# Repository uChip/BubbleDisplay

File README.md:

# hp Bubble Display Controller  

___  

This is a board and firmware project supporting hp's 4 digit 7 segment LED bubble display, QDSP-6064, available from [SparkFun](https://www.sparkfun.com/products/12710).  The project is intended to enable a pair of displays to be easily connected over a two-wire I2C bus to a microcontroller (e.g. Arduino).  The board is also an example circuit of how to get reasonable brightness from these small displays.  By having a separate microcontroller driving the display, the burden (I/O pins, code space & CPU cycles) on the main application microcontroller is reduced.

For a more detailed write-up of the project see "Forum Postings.pdf" in the repo or see [this thread on the SparkFun forum](https://forum.sparkfun.com/viewtopic.php?f=14&t=38056).

Here is a photo of the functional display.  

This repo includes Eagle CAD PCB design files for the board, and Arduino source code for controller firmware and interface library with examples.  The board acts as an I2C slave driven from another microcontroller as I2C master.

## Order PCBs  

You can order this PCB directly from OSH Park.  Click on the following link.  
  * Bubble Display Controller - http://oshpark.com/shared_projects/Lmfa2Fmm 

See Bill of Materials file in repo for parts list.  

## Status  
  * 07APR2014 PCB received built and tested good.
  * Firmware, library and examples have been completed and tested against the final PCB.

## File Formats  

Design files are in "CadSoft EAGLE PCB Design Software" .brd and .sch formats.  
A free version of the software can be downloaded from www.cadsoftusa.com.  

schematic  

PCB   

Firmware, library and examples were developed using the [Arduino](http://arduino.cc/) 1.0.5-r2 IDE and the source files are in Arduino .ino format (and .h or .cpp formats as applicable).

## Distribution License  

You may use this PCB design and source code however you like but no liability is accepted.  

## Attributions

The hardware design has roots in the SparkFun [RedBoard](https://www.sparkfun.com/products/11575) design.  

The firmware is based on the slave_receiver.ino example and relies upon the wire library from Arduino, both included as part of the Arduino distribution.  The SparkFun tutorial [Using the Serial 7-Segment Display](https://learn.sparkfun.com/tutorials/using-the-serial-7-segment-display) was reviewed with an eye toward creating a compatible interface, but in the end it was decided to implement a driver library instead.  Still the tutorial may have influenced this design.  The BubbleDisplay library interface and code were modeled after the Arduino LiquidCrystal library.

## Notes:

This controller board has no serial port for connecting to the Arduino IDE.  The controller firmware is programed using an ISP programer such as the [Pocket AVR Programer](https://www.sparkfun.com/products/9825) from SparkFun.

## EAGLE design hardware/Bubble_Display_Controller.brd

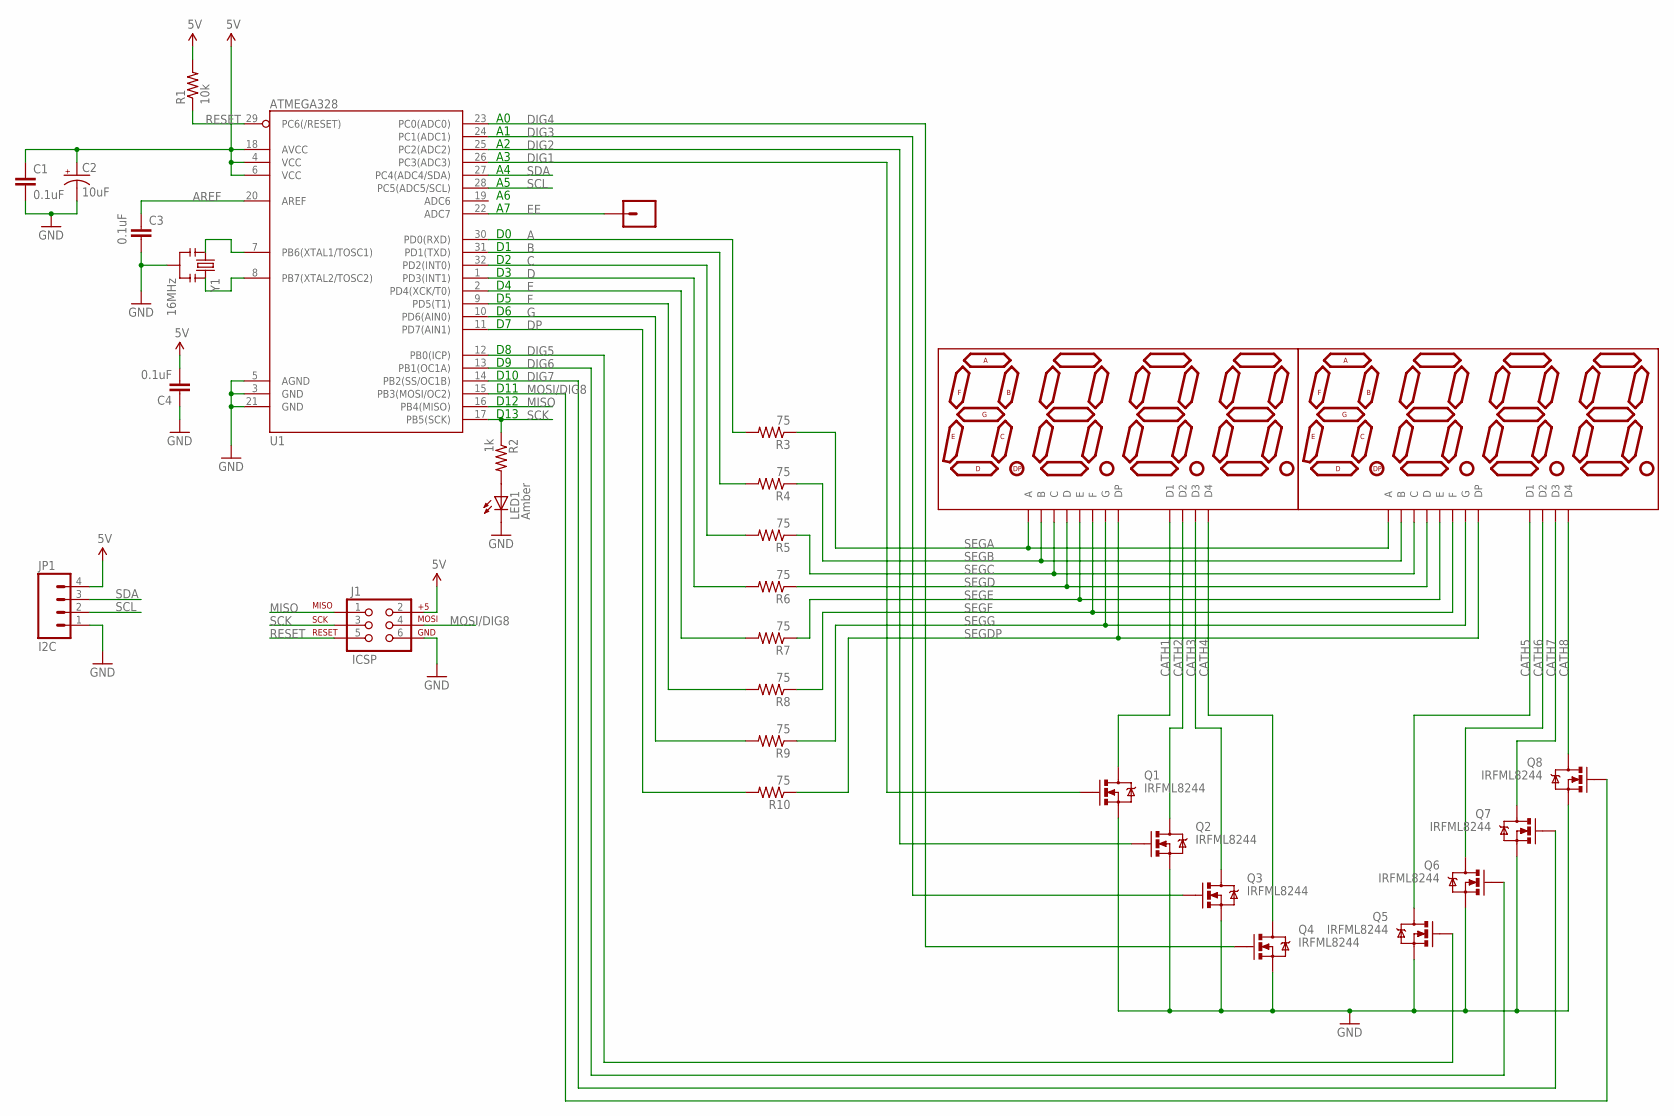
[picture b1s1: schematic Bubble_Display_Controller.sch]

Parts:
C1, C3, C4: 0.1uF; 0805
C2: 10uF; 0805-POL
DISPLAY1, DISPLAY2: hp; DIL12
J1: ICSP; 2X3
JP1: I2C; 1X04
JP2: BREADBD_VIA; BBD-VIA
LED1: Amber; 0805-LED
Q1, Q2, Q3, Q4, Q5, Q6, Q7, Q8: IRFML8244; SOT23
R1: 10k; 0805
R2: 1k; 0805
R3, R4, R5, R6, R7, R8, R9, R10: 75; 0805
U1: ATMEGA328; TQFP32-08
Y1: 16MHz; RESONATOR-SMD

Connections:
5V: C1.1, C2.1 (+), C4.2, J1.2, JP1.4, R1.2, U1.4 (VCC), U1.6 (VCC), U1.18 (AVCC)
A: R3.2, U1.30 (PD0(RXD))
AREF: C3.1, U1.20 (AREF)
B: R4.2, U1.31 (PD1(TXD))
C: R5.2, U1.32 (PD2(INT0))
CATH1: DISPLAY1.1 (D1), Q1.3 (D)
CATH2: DISPLAY1.10 (D2), Q2.3 (D)
CATH3: DISPLAY1.4 (D3), Q3.3 (D)
CATH4: DISPLAY1.6 (D4), Q4.3 (D)
CATH5: DISPLAY2.1 (D1), Q5.3 (D)
CATH6: DISPLAY2.10 (D2), Q6.3 (D)
CATH7: DISPLAY2.4 (D3), Q7.3 (D)
CATH8: DISPLAY2.6 (D4), Q8.3 (D)
D: R6.2, U1.1 (PD3(INT1))
DIG1: Q1.1 (G), U1.26 (PC3(ADC3))
DIG2: Q2.1 (G), U1.25 (PC2(ADC2))
DIG3: Q3.1 (G), U1.24 (PC1(ADC1))
DIG4: Q4.1 (G), U1.23 (PC0(ADC0))
DIG5: Q5.1 (G), U1.12 (PB0(ICP))
DIG6: Q6.1 (G), U1.13 (PB1(OC1A))
DIG7: Q7.1 (G), U1.14 (PB2(SS/OC1B))
DP: R10.2, U1.11 (PD7(AIN1))
E: R7.2, U1.2 (PD4(XCK/T0))
EE: JP2.P$1, U1.22 (ADC7)
F: R8.2, U1.9 (PD5(T1))
G: R9.2, U1.10 (PD6(AIN0))
GND: C1.2, C2.2 (-), C3.2, C4.1, J1.6, JP1.1, LED1.C, Q1.2 (S), Q2.2 (S), Q3.2 (S), Q4.2 (S), Q5.2 (S), Q6.2 (S), Q7.2 (S), Q8.2 (S), U1.3 (GND), U1.5 (AGND), U1.21 (GND), Y1.2
MISO: J1.1, U1.16 (PB4(MISO))
MOSI/DIG8: J1.4, Q8.1 (G), U1.15 (PB3(MOSI/OC2))
unnamed: LED1.A, R2.2
unnamed: U1.7 (PB6(XTAL1/TOSC1)), Y1.1
unnamed: U1.8 (PB7(XTAL2/TOSC2)), Y1.3
RESET: J1.5, R1.1, U1.29 (PC6(/RESET))
SCK: J1.3, R2.1, U1.17 (PB5(SCK))
SCL: JP1.2, U1.28 (PC5(ADC5/SCL))
SDA: JP1.3, U1.27 (PC4(ADC4/SDA))
SEGA: DISPLAY1.12 (A), DISPLAY2.12 (A), R3.1
SEGB: DISPLAY1.11 (B), DISPLAY2.11 (B), R4.1
SEGC: DISPLAY1.3 (C), DISPLAY2.3 (C), R5.1
SEGD: DISPLAY1.8 (D), DISPLAY2.8 (D), R6.1
SEGDP: DISPLAY1.5 (DP), DISPLAY2.5 (DP), R10.1
SEGE: DISPLAY1.2 (E), DISPLAY2.2 (E), R7.1
SEGF: DISPLAY1.9 (F), DISPLAY2.9 (F), R8.1
SEGG: DISPLAY1.7 (G), DISPLAY2.7 (G), R9.1

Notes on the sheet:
D10
D11
D12
D13

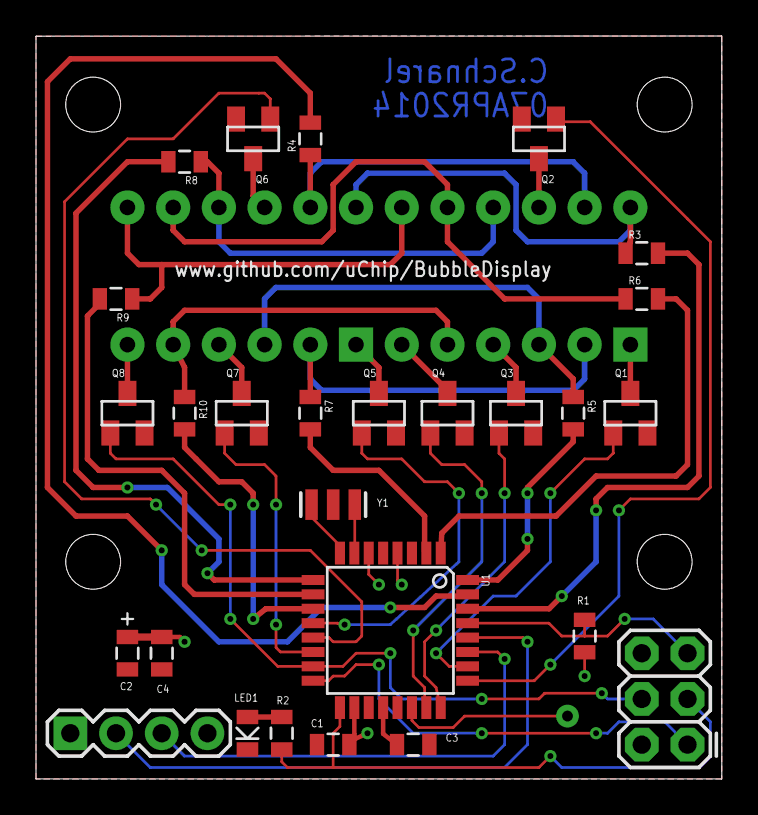
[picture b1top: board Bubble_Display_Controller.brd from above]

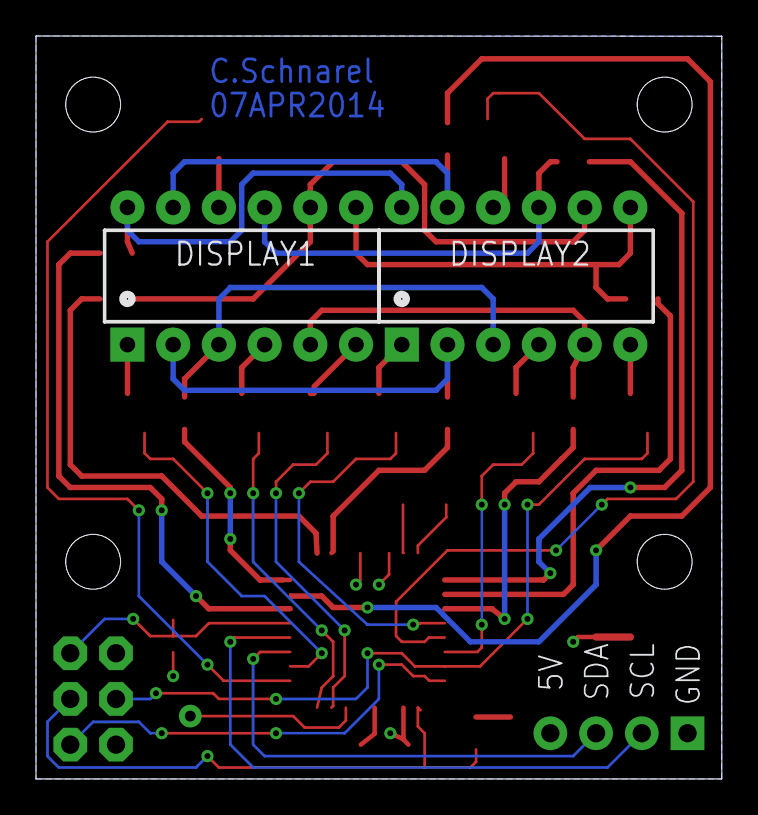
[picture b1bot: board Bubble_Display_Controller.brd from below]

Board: 2 copper layers, 38.1 x 41.3 mm, 34 parts (2 on the bottom side), 44 nets.

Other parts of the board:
U$5, U$6, U$7, U$8: STAND-OFF-TIGHT

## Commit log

2014-03-22 Initial Commit
    Just the hardware files so far
2014-03-22 Updating README w board images
2014-03-30 Updating comp values per simulation. Added BOM. Started firmware.
2014-04-01 Updated to use new HP Display component in my fork of SparkFun libraries
    Also worked on CharGenROM.h; converted segments to HP config. Added
    proper port manipulation to Display_Firmware.ino.
2014-04-02 Some signal name changes
2014-04-06 New version fixing display component bugs
    Changed to correct package definition for display.
    Added mounting holes.
2014-04-07 New HW version started. Bringing FW forward.
2014-04-08 Ordered new board, 8Jyd7Mea. Updating docs to match.
2014-04-08 Firmware update. Better example. Prototype photo
2014-04-12 Creating Library for display controller SW interface
2014-04-15 Changes to get library to compile
    Then changes to example and firmware to match with library.
    Also took new picture of functioning display prototype.
2014-04-16 Software updates
    Tuning library and firmware to work together. Adding Example3 to
    exercise library.
2014-04-17 Beta version of firmware, library and examples
    Reorganized files. Updated docs. Wrote test sketch. Wrote example
    sketches.
2014-04-18 Fixed bug in example ScrollingBanner
2014-04-20 Updates to docs & SW to match new PCB version
2014-04-21 Add example code. Doc updates
    Added setBrightness to library.
    Added examples ported from LCD library.
    Updated BOM to current HW version.
    Updated picture for README.
    Updated docs.
2014-04-21 Last chapter in the posting. Doc updates.
2014-11-04 Changes to CharGenROM character defns
2015-03-02 Fix broken links in README

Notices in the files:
parts and their libraries:
SparkFun-DiscreteSemi: Licensing: Creative Commons ShareAlike 4.0 International - https://creativecommons.org/licenses/by-sa/4.0
SparkFun-FreqCtrl: Licensing: CC v3.0 Share-Alike You are welcome to use this library for commercial purposes.
